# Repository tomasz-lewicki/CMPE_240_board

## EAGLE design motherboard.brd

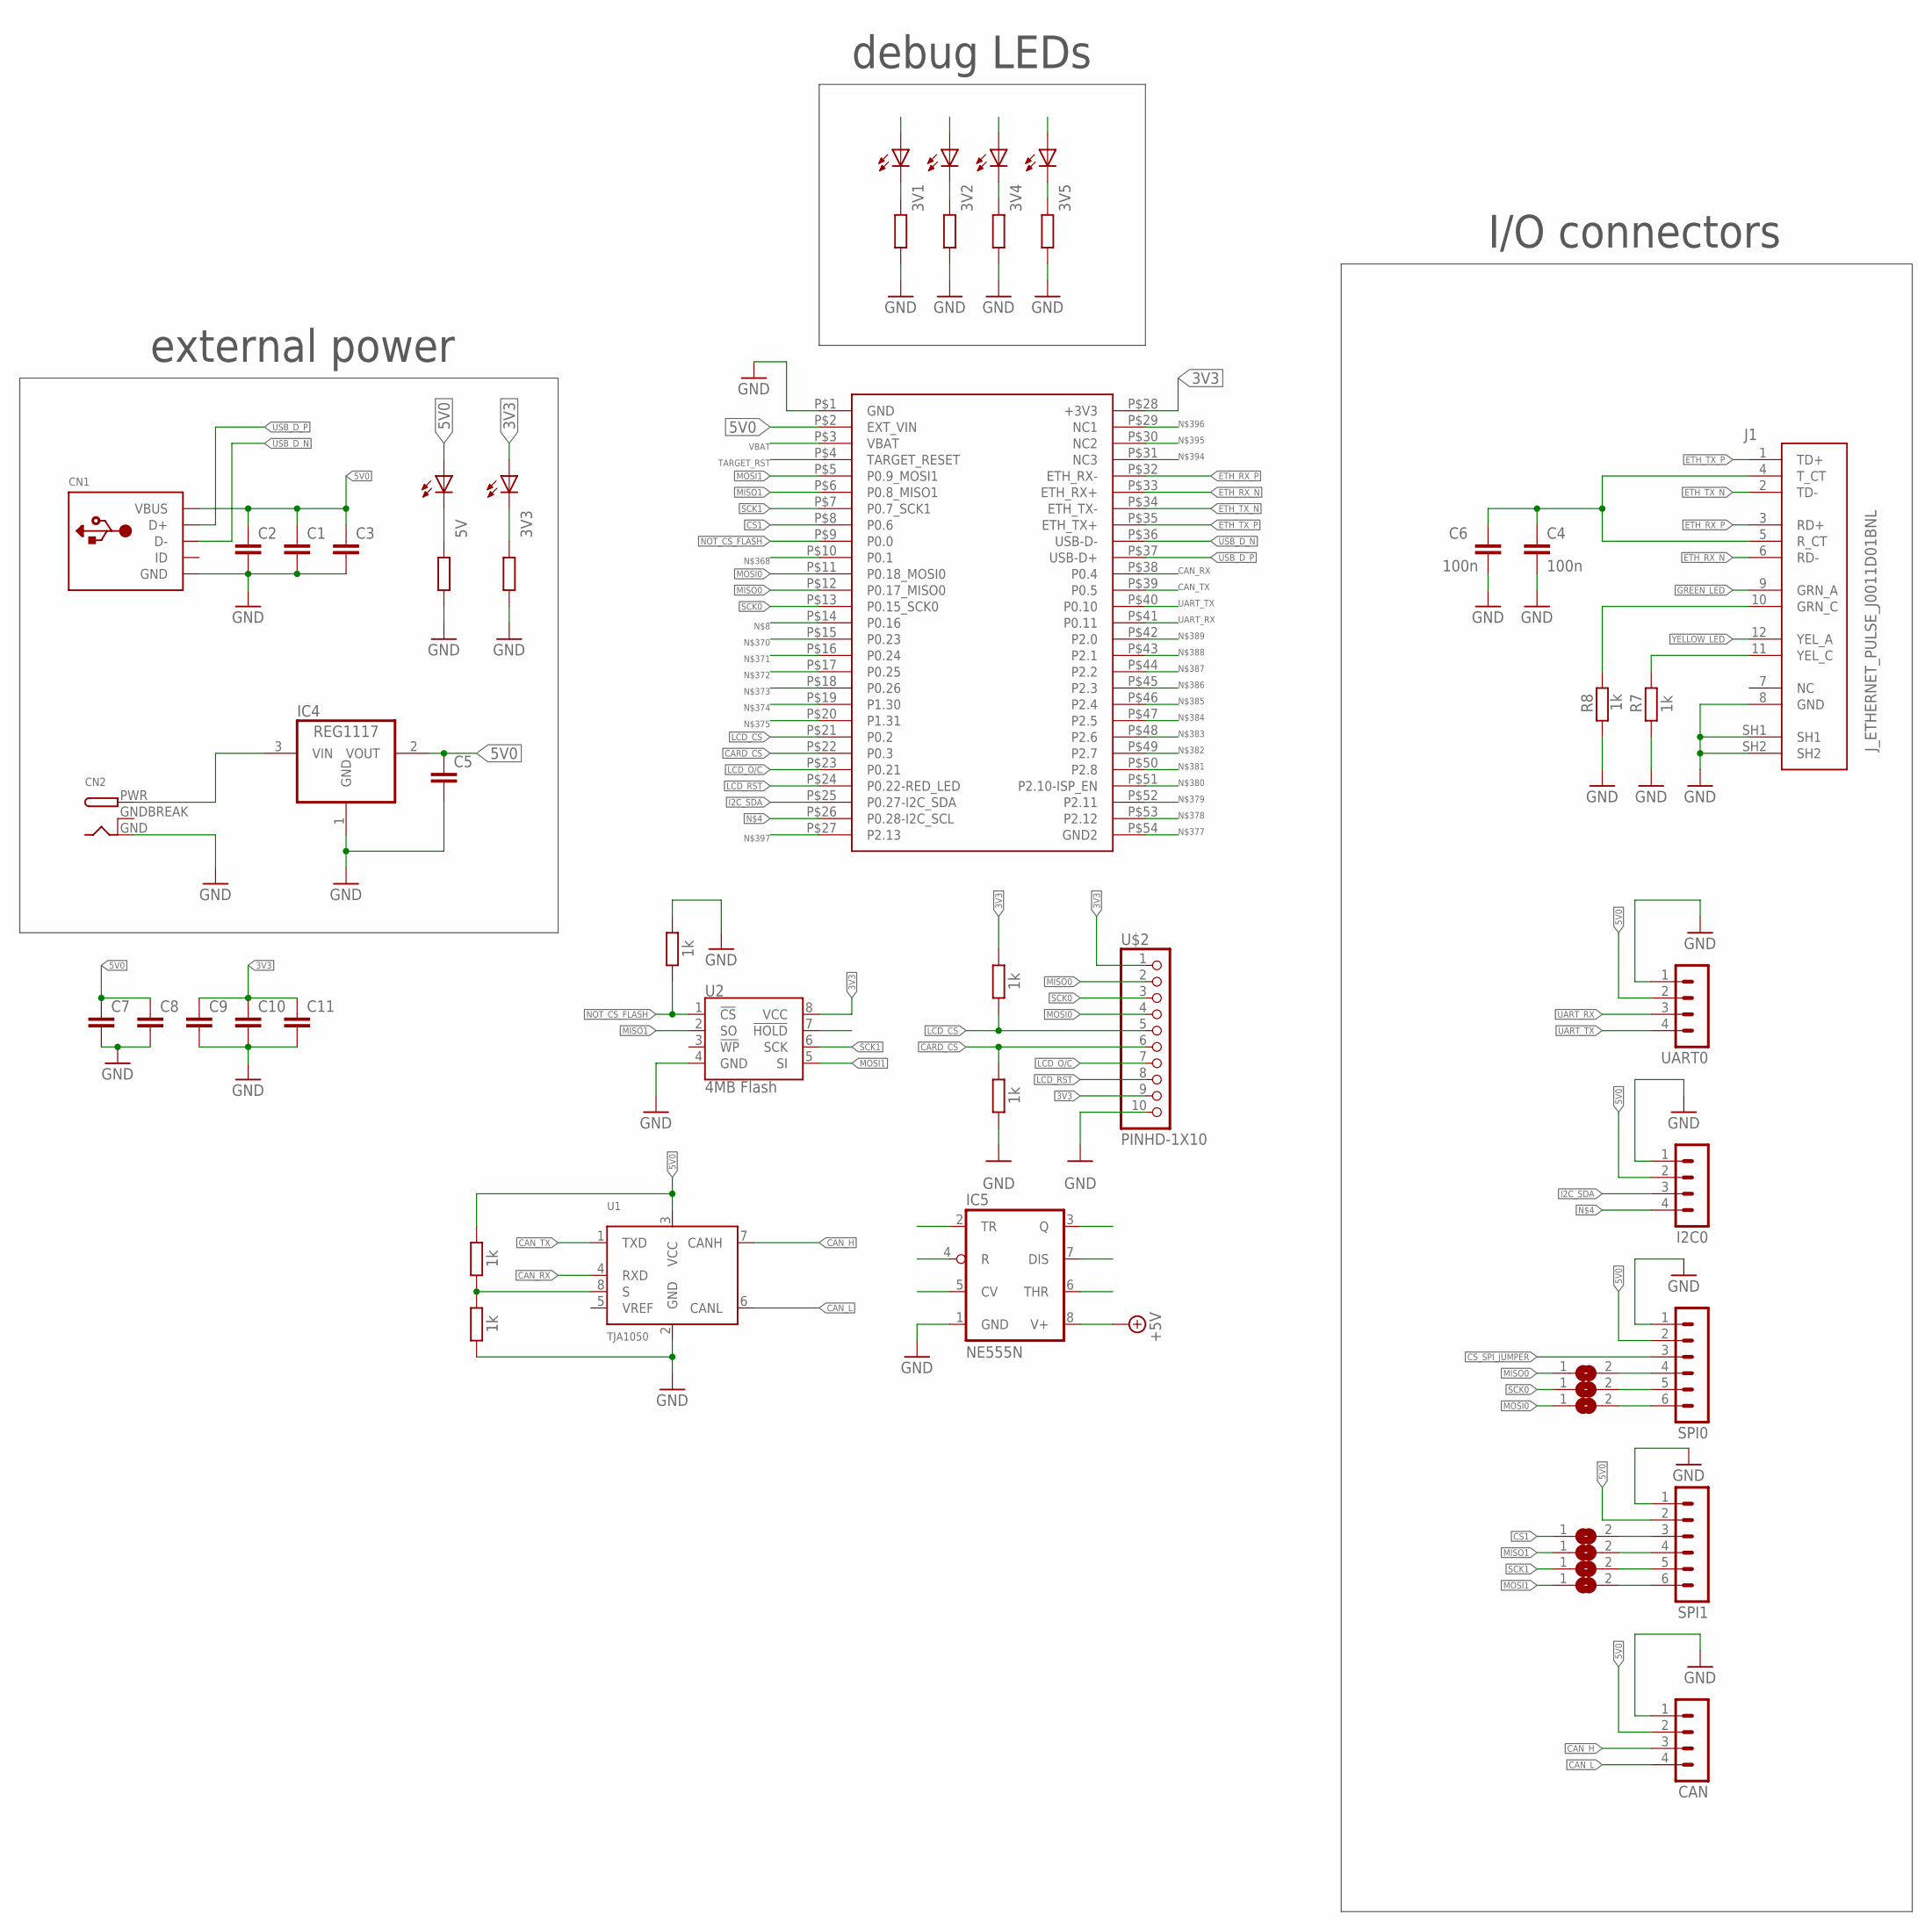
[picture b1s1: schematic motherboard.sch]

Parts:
3V1, 3V2, 3V3, 3V4, 3V5, 5V: LEDCHIPLED_0805; CHIPLED_0805
C1, C2, C3, C5, C7, C8, C9, C10, C11: C-EUC0805K; C0805K
C4, C6: 100n; C0805K
CAN: MA04-1
CN1: USBMINIB; USB-MINIB
CN2: DCBARRELPTH; DCJACK_2MM_PTH
I2C0: MA04-1
IC4: REG1117; SOT223
IC5: NE555N; DIL08
J1: J_ETHERNET_PULSE_J0011D01BNL
R1, R2, R5, R6, R7, R8, R13: 1k; R0805
R3, R4, R9, R10, R11, R12: R-EU_R0805; R0805
SJ1, SJ2, SJ3, SJ5, SJ6, SJ7, SJ8: SJ
SPI0, SPI1: MA06-1
U1: TJA1050; SOT96-1
U2: 4MB Flash; SO08
U$1: LPC1769XPRESSO
U$2: PINHD-1X10; 1X10-BIG
UART0: MA04-1

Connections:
3V1: 3V1.A
3V2: 3V2.A
3V3: 3V3.A, C4.1, C6.1, C9.1, C10.1, C11.1, J1.4 (T_CT), J1.5 (R_CT), R1.2, U2.8 (VCC), U$1.P$28 (+3V3), U$2.1, U$2.9
3V4: 3V4.A
3V5: 3V5.A
5V0: 5V.A, C1.1, C2.1, C3.1, C5.1, C7.1, C8.1, CAN.2, CN1.VBUS, I2C0.2, IC4.2 (VOUT), R6.2, SPI0.2, SPI1.2, U1.3 (VCC), U$1.P$2 (EXT_VIN), UART0.2
12V0: CN2.PWR, IC4.3 (VIN)
+5V: IC5.8 (V+)
CAN_H: CAN.3, U1.7 (CANH)
CAN_L: CAN.4, U1.6 (CANL)
CAN_RX: U1.4 (RXD), U$1.P$38 (P0.4)
CAN_TX: U1.1 (TXD), U$1.P$39 (P0.5)
CARD_CS: R2.2, U$1.P$22 (P0.3), U$2.6
CS1: SJ8.1, U$1.P$8 (P0.6)
CS_SPI_JUMPER: SPI0.3
ETH_RX_N: J1.6 (RD-), U$1.P$33 (ETH_RX+)
ETH_RX_P: J1.3 (RD+), U$1.P$32 (ETH_RX-)
ETH_TX_N: J1.2 (TD-), U$1.P$34 (ETH_TX-)
ETH_TX_P: J1.1 (TD+), U$1.P$35 (ETH_TX+)
GND: C1.2, C2.2, C3.2, C4.2, C5.2, C6.2, C7.2, C8.2, C9.2, C10.2, C11.2, CAN.1, CN1.GND, CN2.GND, I2C0.1, IC4.1 (GND), IC5.1 (GND), J1.8 (GND), J1.SH1, J1.SH2, R2.1, R3.1, R4.1, R5.2, R7.1, R8.1, R9.1, R10.1, R11.1, R12.1, R13.1, SPI0.1, SPI1.1, U1.2 (GND), U2.4 (GND), U$1.P$1 (GND), U$2.10, UART0.1
GNDBREAK: CN2.GNDBREAK
GREEN_LED: J1.9 (GRN_A)
I2C_SDA: I2C0.3, U$1.P$25 (P0.27-I2C_SDA)
LCD_CS: R1.1, U$1.P$21 (P0.2), U$2.5
LCD_O/C: U$1.P$23 (P0.21), U$2.7
LCD_RST: U$1.P$24 (P0.22-RED_LED), U$2.8
MISO0: SJ3.1, U$1.P$12 (P0.17_MISO0), U$2.2
MISO1: SJ7.1, U2.2 (SO), U$1.P$6 (P0.8_MISO1)
MOSI0: SJ1.1, U$1.P$11 (P0.18_MOSI0), U$2.4
MOSI1: SJ5.1, U2.5 (SI), U$1.P$5 (P0.9_MOSI1)
unnamed: 5V.C, R3.2
unnamed: 3V3.C, R4.2
unnamed: I2C0.4, U$1.P$26 (P0.28-I2C_SCL)
unnamed: SJ1.2, SPI0.6
unnamed: SJ2.2, SPI0.5
unnamed: SJ3.2, SPI0.4
unnamed: R6.1, R13.2, U1.8 (S)
unnamed: J1.11 (YEL_C), R7.2
unnamed: J1.10 (GRN_C), R8.2
unnamed: 3V1.C, R9.2
unnamed: 3V2.C, R10.2
unnamed: 3V4.C, R11.2
unnamed: 3V5.C, R12.2
unnamed: SJ5.2, SPI1.6
unnamed: SJ6.2, SPI1.5
unnamed: SJ7.2, SPI1.4
unnamed: SJ8.2, SPI1.3
NOT_CS_FLASH: R5.1, U2.1 (!CS), U$1.P$9 (P0.0)
SCK0: SJ2.1, U$1.P$13 (P0.15_SCK0), U$2.3
SCK1: SJ6.1, U2.6 (SCK), U$1.P$7 (P0.7_SCK1)
TARGET_RST: U$1.P$4 (TARGET_RESET)
UART_RX: U$1.P$41 (P0.11), UART0.3
UART_TX: U$1.P$40 (P0.10), UART0.4
USB_D_N: CN1.D-, U$1.P$36 (USB-D-)
USB_D_P: CN1.D+, U$1.P$37 (USB-D+)
VBAT: U$1.P$3 (VBAT)
YELLOW_LED: J1.12 (YEL_A)

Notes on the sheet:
I/O connectors
debug LEDs
external power

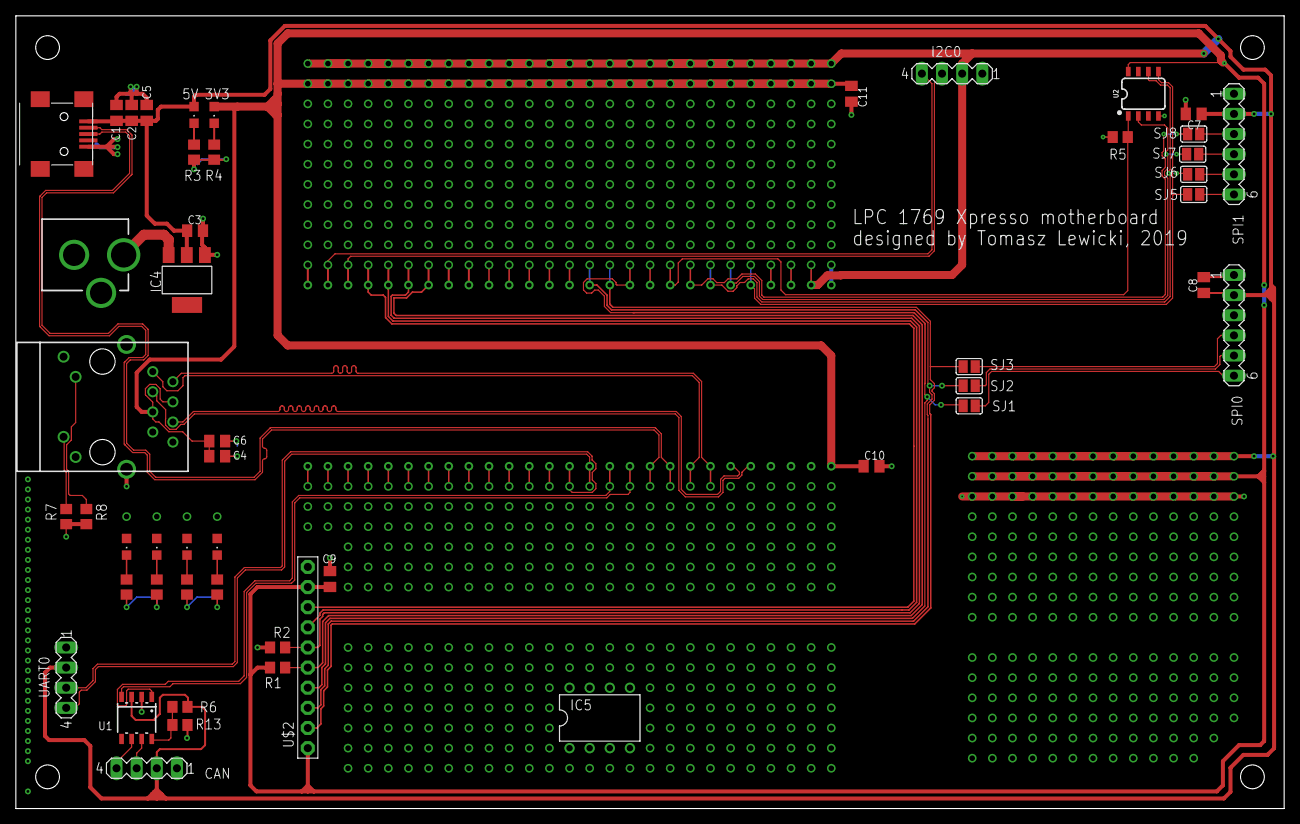
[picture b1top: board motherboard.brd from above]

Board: 2 copper layers, 160.0 x 100.0 mm, 51 parts (0 on the bottom side), 46 nets.

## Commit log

2019-09-11 version with pull-ups for ethernet
2019-09-17 production version

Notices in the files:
parts and their libraries:
NXP_60_26022015: This library may be distributed and adapted freely for any purpose, as long as NXP is credited and any new creation is licensed under the same terms.
SparkFun-IC-Memory: Licensing: Creative Commons ShareAlike 4.0 International - https://creativecommons.org/licenses/by-sa/4.0
